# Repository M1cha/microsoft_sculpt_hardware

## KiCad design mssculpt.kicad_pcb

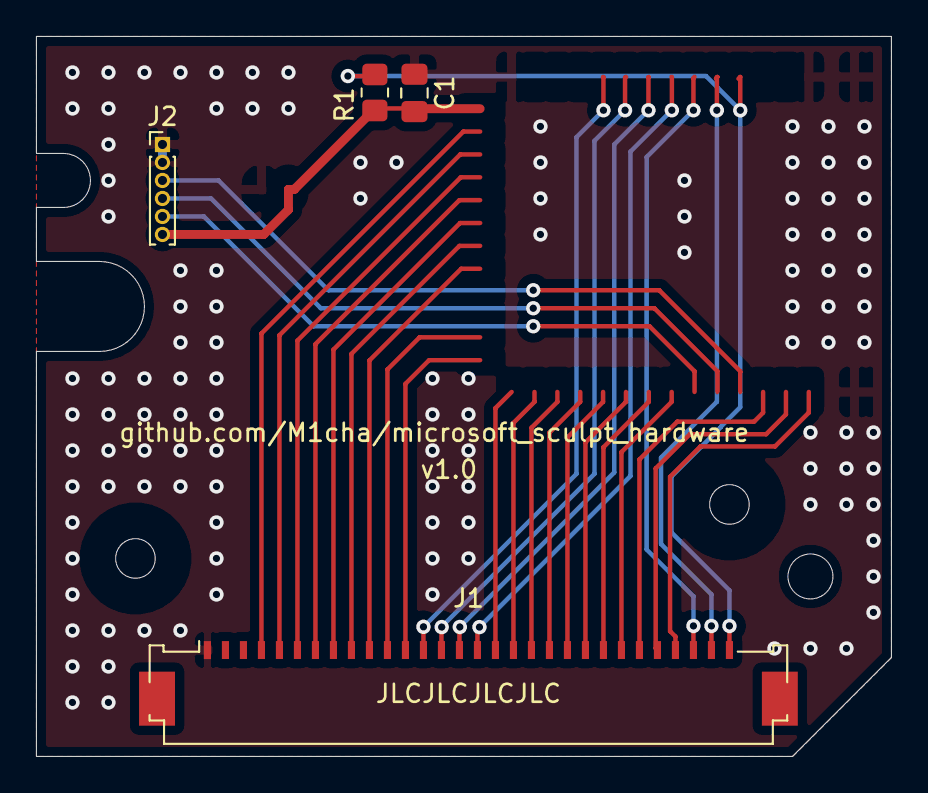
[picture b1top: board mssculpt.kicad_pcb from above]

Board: 2 copper layers, 47.5 x 40.0 mm, 4 parts (0 on the bottom side), 3 nets.

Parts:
C1: C_Small; C_0805_2012Metric_Pad1.18x1.45mm_HandSolder
J1: keyboard; Molex_200528-0300_1x30-1MP_P1.00mm_Horizontal
J2: debug; PinHeader_1x06_P1.00mm_Vertical
R1: R; R_0805_2012Metric_Pad1.20x1.40mm_HandSolder

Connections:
Fn: J1.30, R1.1
GND: C1.1, J1.1, J2.1, J2.2
VCC: C1.2, J2.6, R1.2

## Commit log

2020-11-29 final optimizations
2020-11-29 change export settings
2020-11-29 add jlcpcb order number location
2021-09-17 backup
